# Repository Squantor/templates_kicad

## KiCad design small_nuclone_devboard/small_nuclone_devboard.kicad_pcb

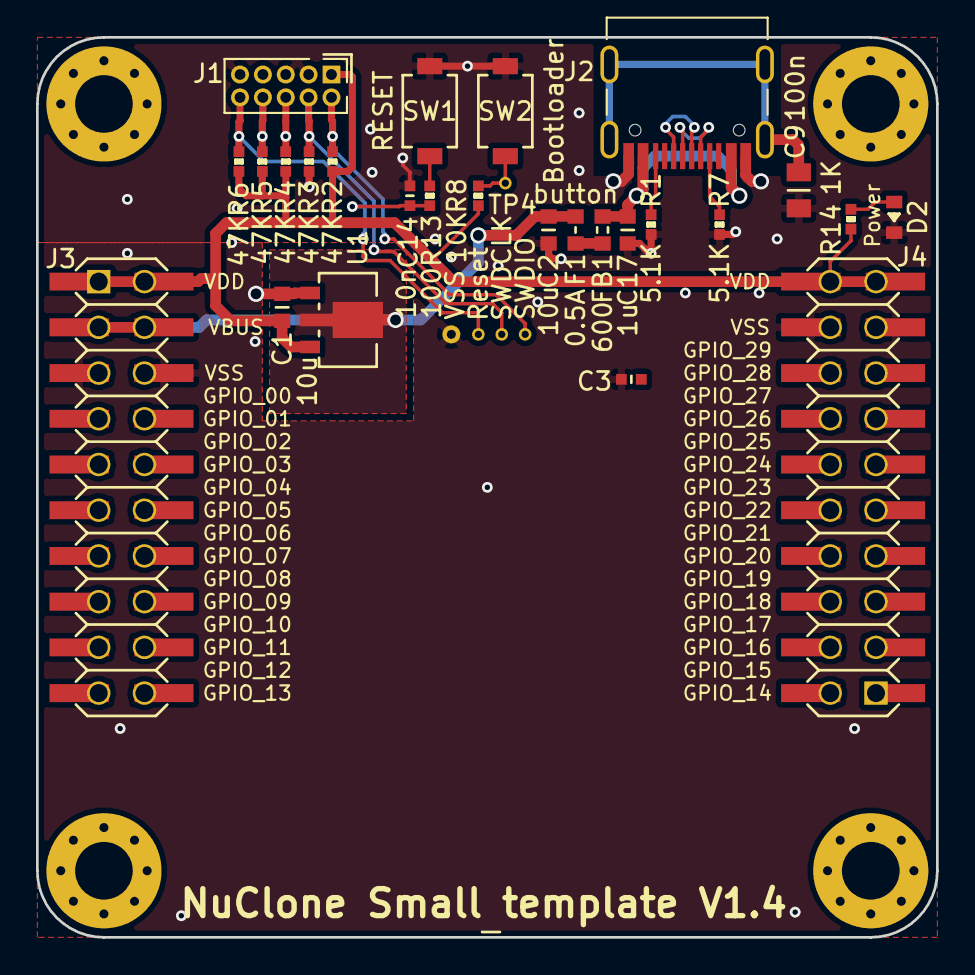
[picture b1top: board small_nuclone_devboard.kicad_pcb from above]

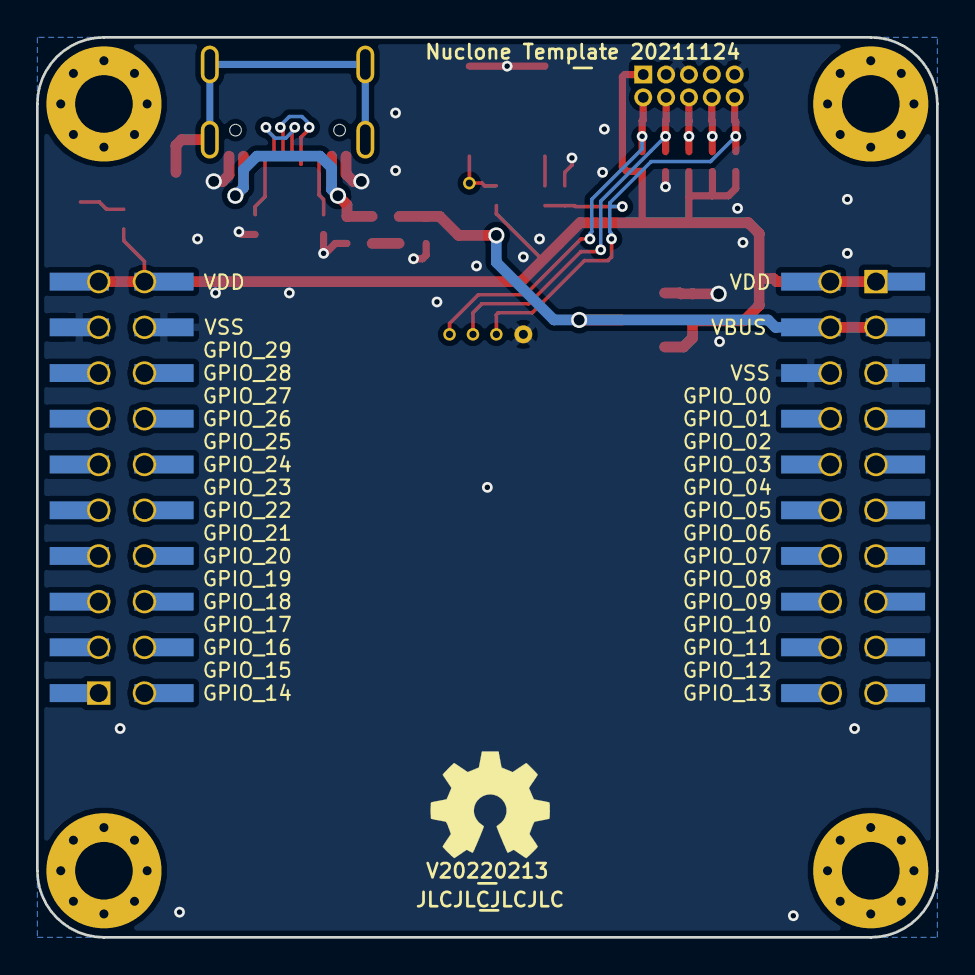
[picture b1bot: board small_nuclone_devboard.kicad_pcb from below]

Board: 2 copper layers, 50.0 x 50.0 mm, 40 parts (4 on the bottom side), 18 nets.

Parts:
C1, C2: 10u; C_0603
C3: 1u; C_0402
C9: 100n; C_0805
C14: 10n; C_0402
C17: 1u; C_0603
D2: GREEN; LED_0603_hand
F1: 0.5A; F_0603_hand
FB1: 600; L_0603
H1, H2, H3, H4: MountingHole; MountingHole_3.2mm_M3_Pad_Via
J1: JTAG_2X05; Header-0127-2X05-H006
J2: TYPE-C-31-M-12; USB-C-HRO-31-M-12
J3: nuclone_small_left; nuclone_small_left_stacked
J4: nuclone_small_right; nuclone_small_right_stacked
N1: OHWLOGO; OSHW-Symbol_6.7x6mm_SilkScreen
N2: V20220213; Label_Generic
N3: JLCJLCJLCJLC; Label_Generic
N4: NuClone Small template V1.4; Label_Generic
N5: Nuclone Template 20211124; Label_Generic
R1, R7: 5.1K; R_0402_hand
R2, R3, R4, R5, R6: 47K; R_0402_hand
R8: 10K; R_0402_hand
R13: 100; R_0402_hand
R14: 1K; R_0402_hand
SW1: RESET; TD-85XU
SW2: Bootloader; TD-85XU
TP1: SWDIO; TestPoint_hole_H04R07
TP2: SWDCLK; TestPoint_hole_H04R07
TP3: VSS; TestPoint_hole_H05R10
TP4: button; TestPoint_hole_H04R07
TP5: Reset; TestPoint_hole_H04R07
U1: MCP1702-MB; SOT89-NXP

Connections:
/Bootloader: R8.1, SW2.2, TP4.1
/RESET: C14.2, J1.10, R6.1, R13.1, TP5.1
/TCK: J1.4, R3.1, TP2.1
/TDI: J1.8, R5.1
/TDO: J1.6, R4.1
/TMS: J1.2, R2.1, TP1.1
/VBUS: C2.2, F1.1, J3.3, J3.4, U1.2
/VDD: C1.1, C3.1, J1.1, J3.1, J3.2, J4.19, J4.20, R2.2, R4.2, R5.2, R6.2, R8.2, R14.2, U1.3
/VSS: C1.2, C2.1, C3.2, C9.1, C14.1, C17.1, D2.1, J1.3, J1.5, J1.9, J2.A1B12, J2.B1A12, J3.5, J3.6, J4.17, J4.18, R1.1, R3.2, R7.1, SW1.1, SW2.1, TP3.1, U1.1
unnamed: C9.2, J2.S
unnamed: C17.2, FB1.2, J2.A4B9, J2.B4A9
unnamed: D2.2, R14.1
unnamed: F1.2, FB1.1
unnamed: J2.A5, R7.2
unnamed: J2.A6, J2.B6
unnamed: J2.A7, J2.B7
unnamed: J2.B5, R1.2
unnamed: R13.2, SW1.2

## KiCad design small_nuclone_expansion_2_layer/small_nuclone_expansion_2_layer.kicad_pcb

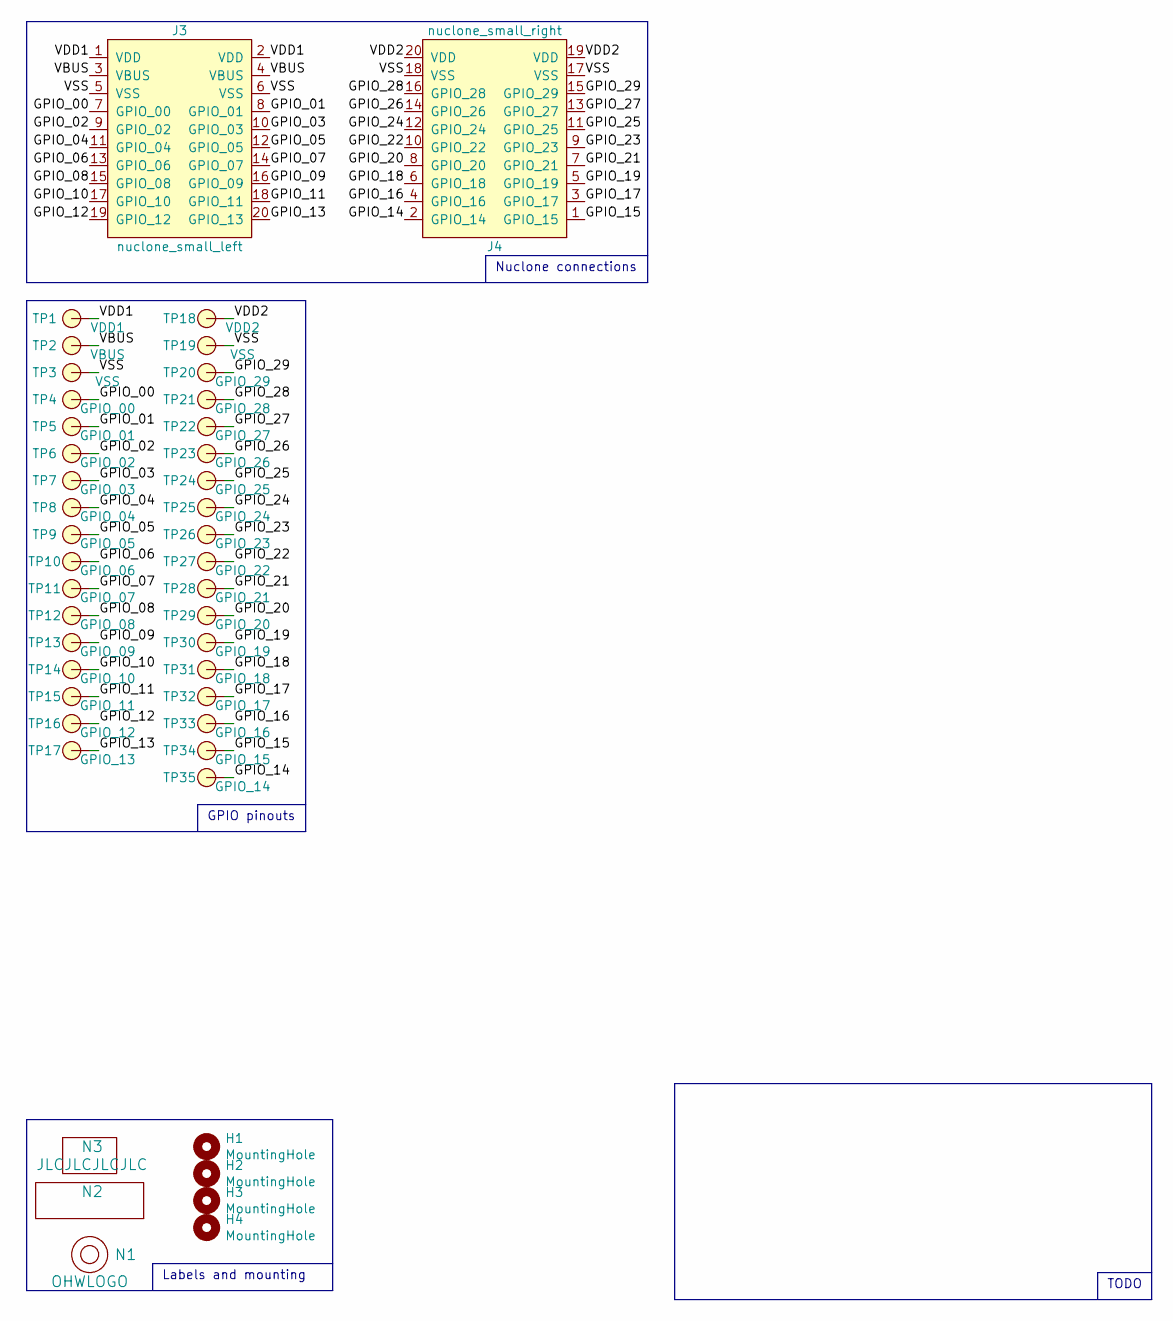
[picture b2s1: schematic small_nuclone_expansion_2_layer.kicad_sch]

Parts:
H1, H2, H3, H4: MountingHole; MountingHole_3.2mm_M3_Pad_Via
J3: nuclone_small_left; nuclone_small_left_stacked
J4: nuclone_small_right; nuclone_small_right_stacked
N1: OHWLOGO; OSHW-Symbol_6.7x6mm_SilkScreen
N2: Label_Generic
N3: JLCJLCJLCJLC; Label_Generic
TP1: VDD1; TestPoint_hole_H05R10_2side
TP2: VBUS; TestPoint_hole_H05R10_2side
TP3, TP19: VSS; TestPoint_hole_H05R10_2side
TP4: GPIO_00; TestPoint_hole_H05R10_2side
TP5: GPIO_01; TestPoint_hole_H05R10_2side
TP6: GPIO_02; TestPoint_hole_H05R10_2side
TP7: GPIO_03; TestPoint_hole_H05R10_2side
TP8: GPIO_04; TestPoint_hole_H05R10_2side
TP9: GPIO_05; TestPoint_hole_H05R10_2side
TP10: GPIO_06; TestPoint_hole_H05R10_2side
TP11: GPIO_07; TestPoint_hole_H05R10_2side
TP12: GPIO_08; TestPoint_hole_H05R10_2side
TP13: GPIO_09; TestPoint_hole_H05R10_2side
TP14: GPIO_10; TestPoint_hole_H05R10_2side
TP15: GPIO_11; TestPoint_hole_H05R10_2side
TP16: GPIO_12; TestPoint_hole_H05R10_2side
TP17: GPIO_13; TestPoint_hole_H05R10_2side
TP18: VDD2; TestPoint_hole_H05R10_2side
TP20: GPIO_29; TestPoint_hole_H05R10_2side
TP21: GPIO_28; TestPoint_hole_H05R10_2side
TP22: GPIO_27; TestPoint_hole_H05R10_2side
TP23: GPIO_26; TestPoint_hole_H05R10_2side
TP24: GPIO_25; TestPoint_hole_H05R10_2side
TP25: GPIO_24; TestPoint_hole_H05R10_2side
TP26: GPIO_23; TestPoint_hole_H05R10_2side
TP27: GPIO_22; TestPoint_hole_H05R10_2side
TP28: GPIO_21; TestPoint_hole_H05R10_2side
TP29: GPIO_20; TestPoint_hole_H05R10_2side
TP30: GPIO_19; TestPoint_hole_H05R10_2side
TP31: GPIO_18; TestPoint_hole_H05R10_2side
TP32: GPIO_17; TestPoint_hole_H05R10_2side
TP33: GPIO_16; TestPoint_hole_H05R10_2side
TP34: GPIO_15; TestPoint_hole_H05R10_2side
TP35: GPIO_14; TestPoint_hole_H05R10_2side

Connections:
/GPIO_00: J3.7 (GPIO_00), TP4.1
/GPIO_01: J3.8 (GPIO_01), TP5.1
/GPIO_02: J3.9 (GPIO_02), TP6.1
/GPIO_03: J3.10 (GPIO_03), TP7.1
/GPIO_04: J3.11 (GPIO_04), TP8.1
/GPIO_05: J3.12 (GPIO_05), TP9.1
/GPIO_06: J3.13 (GPIO_06), TP10.1
/GPIO_07: J3.14 (GPIO_07), TP11.1
/GPIO_08: J3.15 (GPIO_08), TP12.1
/GPIO_09: J3.16 (GPIO_09), TP13.1
/GPIO_10: J3.17 (GPIO_10), TP14.1
/GPIO_11: J3.18 (GPIO_11), TP15.1
/GPIO_12: J3.19 (GPIO_12), TP16.1
/GPIO_13: J3.20 (GPIO_13), TP17.1
/GPIO_14: J4.2 (GPIO_14), TP35.1
/GPIO_15: J4.1 (GPIO_15), TP34.1
/GPIO_16: J4.4 (GPIO_16), TP33.1
/GPIO_17: J4.3 (GPIO_17), TP32.1
/GPIO_18: J4.6 (GPIO_18), TP31.1
/GPIO_19: J4.5 (GPIO_19), TP30.1
/GPIO_20: J4.8 (GPIO_20), TP29.1
/GPIO_21: J4.7 (GPIO_21), TP28.1
/GPIO_22: J4.10 (GPIO_22), TP27.1
/GPIO_23: J4.9 (GPIO_23), TP26.1
/GPIO_24: J4.12 (GPIO_24), TP25.1
/GPIO_25: J4.11 (GPIO_25), TP24.1
/GPIO_26: J4.14 (GPIO_26), TP23.1
/GPIO_27: J4.13 (GPIO_27), TP22.1
/GPIO_28: J4.16 (GPIO_28), TP21.1
/GPIO_29: J4.15 (GPIO_29), TP20.1
/VBUS: J3.3 (VBUS), J3.4 (VBUS), TP2.1
/VDD1: J3.1 (VDD), J3.2 (VDD), TP1.1
/VDD2: J4.19 (VDD), J4.20 (VDD), TP18.1
/VSS: J3.5 (VSS), J3.6 (VSS), J4.17 (VSS), J4.18 (VSS), TP3.1, TP19.1

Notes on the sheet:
Nuclone connections
TODO
Labels and mounting
GPIO pinouts

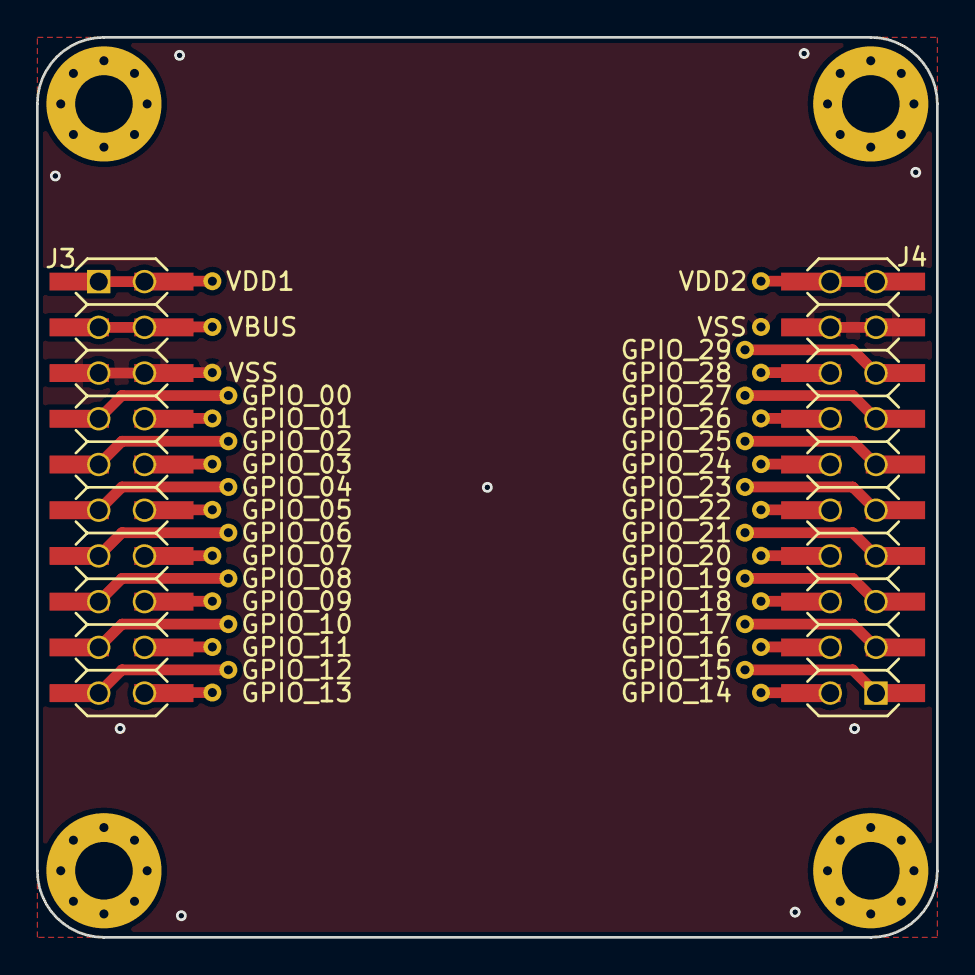
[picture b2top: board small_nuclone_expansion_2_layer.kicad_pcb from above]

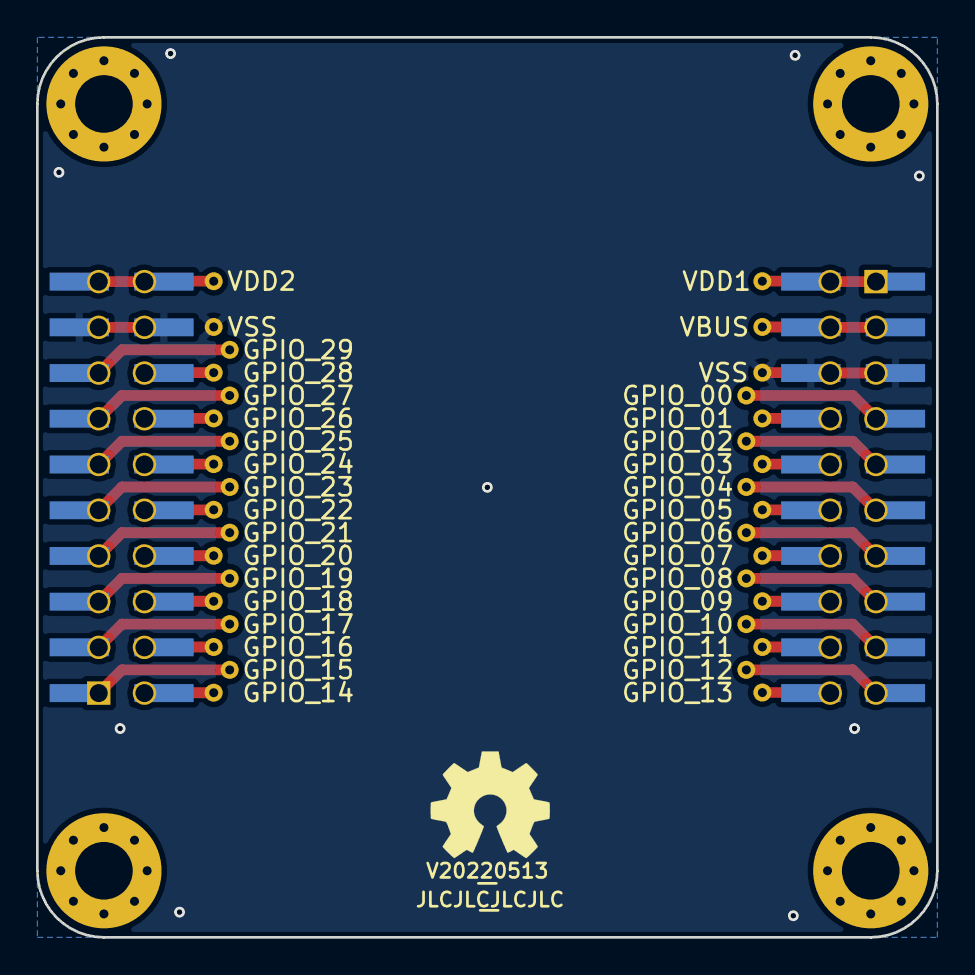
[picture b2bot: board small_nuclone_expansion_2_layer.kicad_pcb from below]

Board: 2 copper layers, 50.0 x 50.0 mm, 44 parts (3 on the bottom side), 34 nets.

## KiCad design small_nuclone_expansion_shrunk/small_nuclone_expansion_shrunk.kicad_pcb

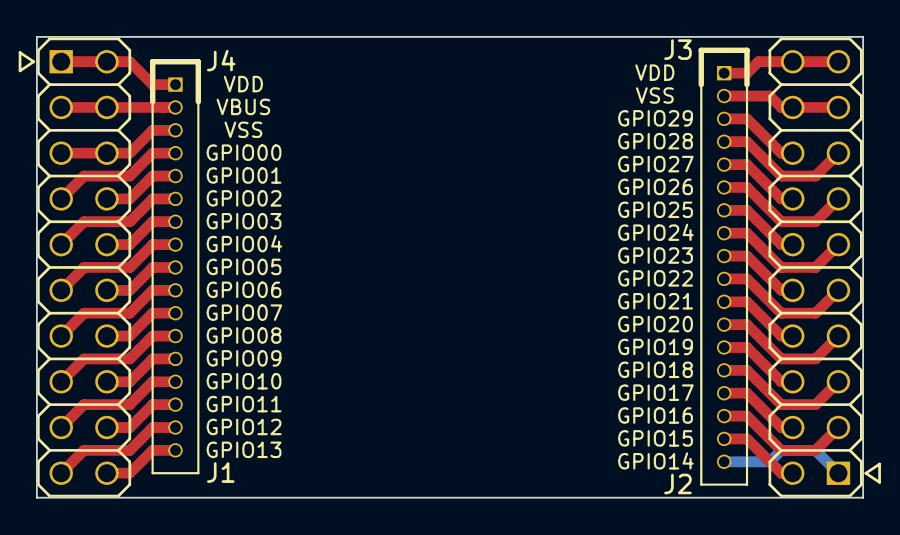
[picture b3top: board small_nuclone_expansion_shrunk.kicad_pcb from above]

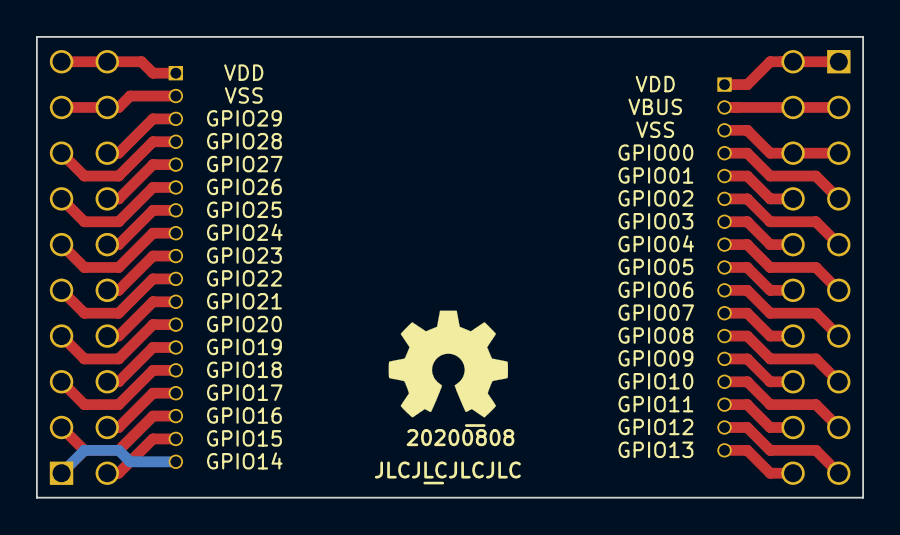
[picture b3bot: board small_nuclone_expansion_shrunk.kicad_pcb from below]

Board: 2 copper layers, 45.9 x 25.6 mm, 7 parts (3 on the bottom side), 35 nets.

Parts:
J1: nuclone_small_left; Header-0254-2X10-H010
J2: nuclone_small_right; Header-0254-2X10-H010
J3: PINS_1X18; Header-0127-1X18-H006
J4: PINS_1X17; Header-0127-1X17-H006
N1: OHWLOGO; OSHW-Symbol_6.7x6mm_SilkScreen
N2: 20200808; Label_Generic
N3: JLCJLCJLCJLC; Label_Generic

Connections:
/GPIO_00: J1.7, J4.4
/GPIO_01: J1.8, J4.5
/GPIO_02: J1.9, J4.6
/GPIO_03: J1.10, J4.7
/GPIO_04: J1.11, J4.8
/GPIO_05: J1.12, J4.9
/GPIO_06: J1.13, J4.10
/GPIO_07: J1.14, J4.11
/GPIO_08: J1.15, J4.12
/GPIO_09: J1.16, J4.13
/GPIO_10: J1.17, J4.14
/GPIO_11: J1.18, J4.15
/GPIO_12: J1.19, J4.16
/GPIO_13: J1.20, J4.17
/GPIO_14: J2.1, J3.18
/GPIO_15: J2.2, J3.17
/GPIO_16: J2.3, J3.16
/GPIO_17: J2.4, J3.15
/GPIO_18: J2.5, J3.14
/GPIO_19: J2.6, J3.13
/GPIO_20: J2.7, J3.12
/GPIO_21: J2.8, J3.11
/GPIO_22: J2.9, J3.10
/GPIO_23: J2.10, J3.9
/GPIO_24: J2.11, J3.8
/GPIO_25: J2.12, J3.7
/GPIO_26: J2.13, J3.6
/GPIO_27: J2.14, J3.5
/GPIO_28: J2.15, J3.4
/GPIO_29: J2.16, J3.3
/VBUS: J1.3, J1.4, J4.2
/VDD1: J1.1, J1.2, J4.1
/VDD2: J2.19, J2.20, J3.1
/VSS1: J1.5, J1.6, J4.3
/VSS2: J2.17, J2.18, J3.2
